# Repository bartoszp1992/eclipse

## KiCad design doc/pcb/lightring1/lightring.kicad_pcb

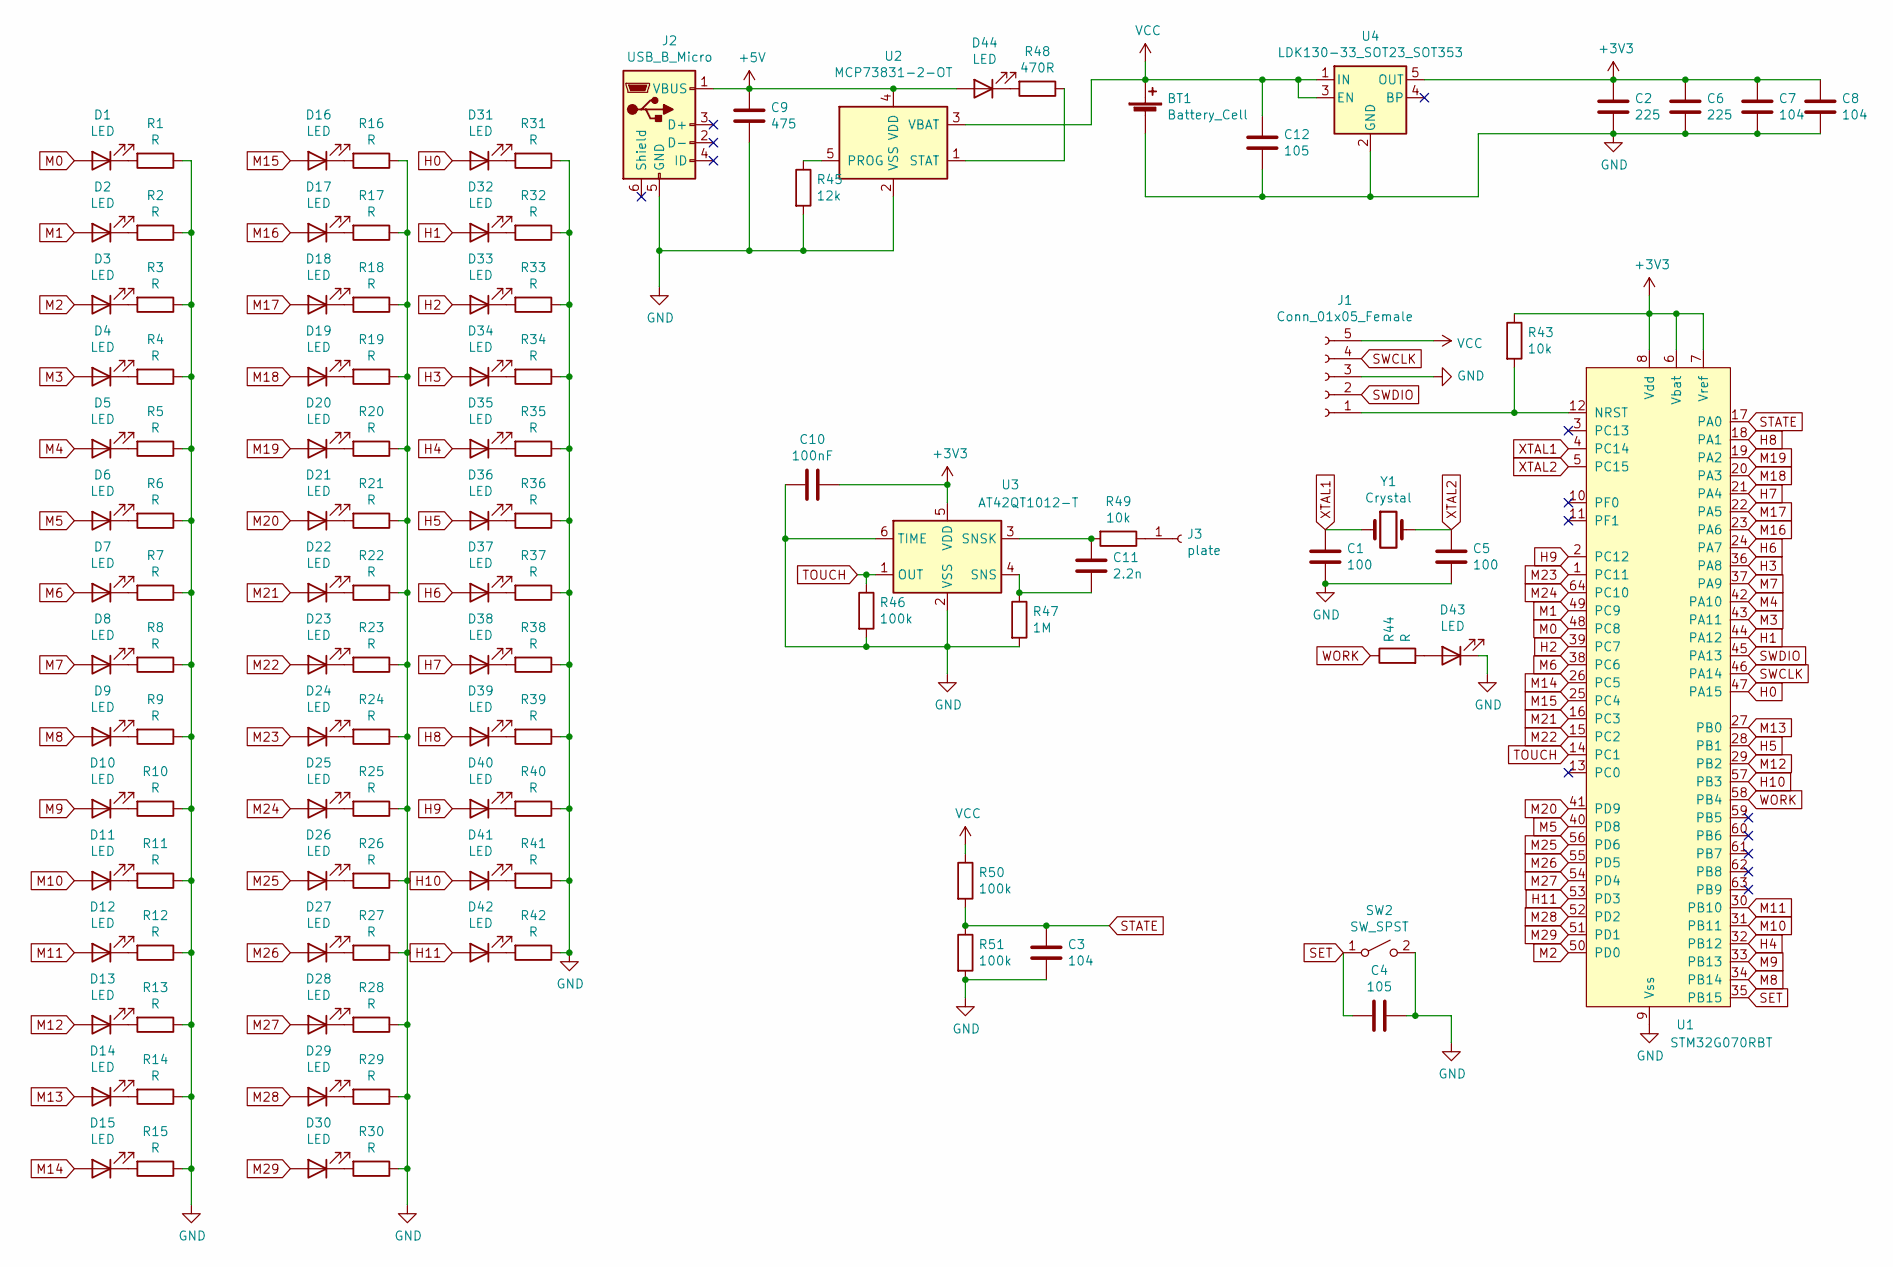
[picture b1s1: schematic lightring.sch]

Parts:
BT1: Battery_Cell; R_1210_3225Metric
C1, C5: 100; C_0603_1608Metric
C2, C6: 225; C_0603_1608Metric
C3, C7, C8: 104; C_0603_1608Metric
C4, C12: 105; C_0603_1608Metric
C9: 475; C_0603_1608Metric
C10: 100nF; C_0603_1608Metric
C11: 2.2n; C_0603_1608Metric
D1, D2, D3, D4, D5, D6, D7, D8, D9, D10, D11, D12, D13, D14, D15, D16, D17, D18, D19, D20, D21, D22, D23, D24, D25, D26, D27, D28, D29, D30, D31, D32, D33, D34, D35, D36, D37, D38, D39, D40, D41, D42, D43: LED; LR_LED
D44: LED; D_0603_1608Metric
J1: Conn_01x05_Female; PinHeader_1x05_P1.27mm_Vertical
J2: USB_B_Micro; USB_Micro-B_Molex_47346-0001
J3: plate; touchplate
R1, R2, R3, R4, R5, R6, R7, R8, R9, R10, R11, R12, R13, R14, R15, R16, R17, R18, R19, R20, R21, R22, R23, R24, R25, R26, R27, R28, R29, R30, R31, R32, R33, R34, R35, R36, R37, R38, R39, R40, R41, R42: R; LR_RES
R43, R49: 10k; R_0603_1608Metric
R44: R; R_0603_1608Metric
R45: 12k; R_0603_1608Metric
R46, R50, R51: 100k; R_0603_1608Metric
R47: 1M; R_0603_1608Metric
R48: 470R; R_0603_1608Metric
SW2: SW_SPST; Panasonic_EVQPUJ_EVQPUA
U1: STM32G070RBT; LQFP-64_10x10mm_P0.5mm
U2: MCP73831-2-OT; SOT-23-5
U3: AT42QT1012-T; SOT-23-6
U4: LDK130-33_SOT23_SOT353; SOT-23-5
Y1: Crystal; Crystal_C26-LF_D2.1mm_L6.5mm_Horizontal

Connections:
+3V3: C2.1, C6.1, C7.1, C8.1, C10.1, R43.1, U1.6 (Vbat), U1.7 (Vref), U1.8 (Vdd), U3.5 (VDD), U4.5 (OUT)
+5V: C9.1, D44.2 (A), J2.1 (VBUS), U2.4 (VDD)
GND: BT1.2 (-), C1.2, C2.2, C3.2, C4.1, C5.2, C6.2, C7.2, C8.2, C9.2, C10.2, C12.2, D43.1 (K), J1.3, J2.5 (GND), R1.1, R2.1, R3.1, R4.1, R5.1, R6.1, R7.1, R8.1, R9.1, R10.1, R11.1, R12.1, R13.1, R14.1, R15.1, R16.1, R17.1, R18.1, R19.1, R20.1, R21.1, R22.1, R23.1, R24.1, R25.1, R26.1, R27.1, R28.1, R29.1, R30.1, R31.1, R32.1, R33.1, R34.1, R35.1, R36.1, R37.1, R38.1, R39.1, R40.1, R41.1, R42.1, R45.2, R46.2, R47.2, R51.2, SW2.2 (B), U1.9 (Vss), U2.2 (VSS), U3.2 (VSS), U3.6 (TIME), U4.2 (GND)
H0: D31.2 (A), U1.47 (PA15)
H1: D32.2 (A), U1.44 (PA12)
H2: D33.2 (A), U1.39 (PC7)
H3: D34.2 (A), U1.36 (PA8)
H4: D35.2 (A), U1.32 (PB12)
H5: D36.2 (A), U1.28 (PB1)
H6: D37.2 (A), U1.24 (PA7)
H7: D38.2 (A), U1.21 (PA4)
H8: D39.2 (A), U1.18 (PA1)
H9: D40.2 (A), U1.2 (PC12)
H10: D41.2 (A), U1.57 (PB3)
H11: D42.2 (A), U1.53 (PD3)
M0: D1.2 (A), U1.48 (PC8)
M1: D2.2 (A), U1.49 (PC9)
M2: D3.2 (A), U1.50 (PD0)
M3: D4.2 (A), U1.43 (PA11)
M4: D5.2 (A), U1.42 (PA10)
M5: D6.2 (A), U1.40 (PD8)
M6: D7.2 (A), U1.38 (PC6)
M7: D8.2 (A), U1.37 (PA9)
M8: D9.2 (A), U1.34 (PB14)
M9: D10.2 (A), U1.33 (PB13)
M10: D11.2 (A), U1.31 (PB11)
M11: D12.2 (A), U1.30 (PB10)
M12: D13.2 (A), U1.29 (PB2)
M13: D14.2 (A), U1.27 (PB0)
M14: D15.2 (A), U1.26 (PC5)
M15: D16.2 (A), U1.25 (PC4)
M16: D17.2 (A), U1.23 (PA6)
M17: D18.2 (A), U1.22 (PA5)
M18: D19.2 (A), U1.20 (PA3)
M19: D20.2 (A), U1.19 (PA2)
M20: D21.2 (A), U1.41 (PD9)
M21: D22.2 (A), U1.16 (PC3)
M22: D23.2 (A), U1.15 (PC2)
M23: D24.2 (A), U1.1 (PC11)
M24: D25.2 (A), U1.64 (PC10)
M25: D26.2 (A), U1.56 (PD6)
M26: D27.2 (A), U1.55 (PD5)
M27: D28.2 (A), U1.54 (PD4)
M28: D29.2 (A), U1.52 (PD2)
M29: D30.2 (A), U1.51 (PD1)
unnamed: C11.1, R49.2, U3.3 (SNSK)
unnamed: C11.2, R47.1, U3.4 (SNS)
unnamed: D1.1 (K), R1.2
unnamed: D2.1 (K), R2.2
unnamed: D3.1 (K), R3.2
unnamed: D4.1 (K), R4.2
unnamed: D5.1 (K), R5.2
unnamed: D6.1 (K), R6.2
unnamed: D7.1 (K), R7.2
unnamed: D8.1 (K), R8.2
unnamed: D9.1 (K), R9.2
unnamed: D10.1 (K), R10.2
unnamed: D11.1 (K), R11.2
unnamed: D12.1 (K), R12.2
unnamed: D13.1 (K), R13.2
unnamed: D14.1 (K), R14.2
unnamed: D15.1 (K), R15.2
unnamed: D16.1 (K), R16.2
unnamed: D17.1 (K), R17.2
unnamed: D18.1 (K), R18.2
unnamed: D19.1 (K), R19.2
unnamed: D20.1 (K), R20.2
unnamed: D21.1 (K), R21.2
unnamed: D22.1 (K), R22.2
unnamed: D23.1 (K), R23.2
unnamed: D24.1 (K), R24.2
unnamed: D25.1 (K), R25.2
unnamed: D26.1 (K), R26.2
unnamed: D27.1 (K), R27.2
unnamed: D28.1 (K), R28.2
unnamed: D29.1 (K), R29.2
unnamed: D30.1 (K), R30.2
unnamed: D31.1 (K), R31.2
unnamed: D32.1 (K), R32.2
unnamed: D33.1 (K), R33.2
unnamed: D34.1 (K), R34.2
unnamed: D35.1 (K), R35.2
unnamed: D36.1 (K), R36.2
unnamed: D37.1 (K), R37.2
unnamed: D38.1 (K), R38.2
unnamed: D39.1 (K), R39.2
unnamed: D40.1 (K), R40.2
unnamed: D41.1 (K), R41.2
unnamed: D42.1 (K), R42.2
unnamed: D43.2 (A), R44.2
unnamed: D44.1 (K), R48.2
unnamed: J1.1, R43.2, U1.12 (NRST)
unnamed: J3.1, R49.1
unnamed: R45.1, U2.5 (PROG)
unnamed: R48.1, U2.1 (STAT)
SET: C4.2, SW2.1 (A), U1.35 (PB15)
STATE: C3.1, R50.2, R51.1, U1.17 (PA0)
SWCLK: J1.4, U1.46 (PA14)
SWDIO: J1.2, U1.45 (PA13)
TOUCH: R46.1, U1.14 (PC1), U3.1 (OUT)
VCC: BT1.1 (+), C12.1, J1.5, R50.1, U2.3 (VBAT), U4.1 (IN), U4.3 (EN)
WORK: R44.1, U1.58 (PB4)
XTAL1: C1.1, U1.4 (PC14), Y1.1
XTAL2: C5.1, U1.5 (PC15), Y1.2

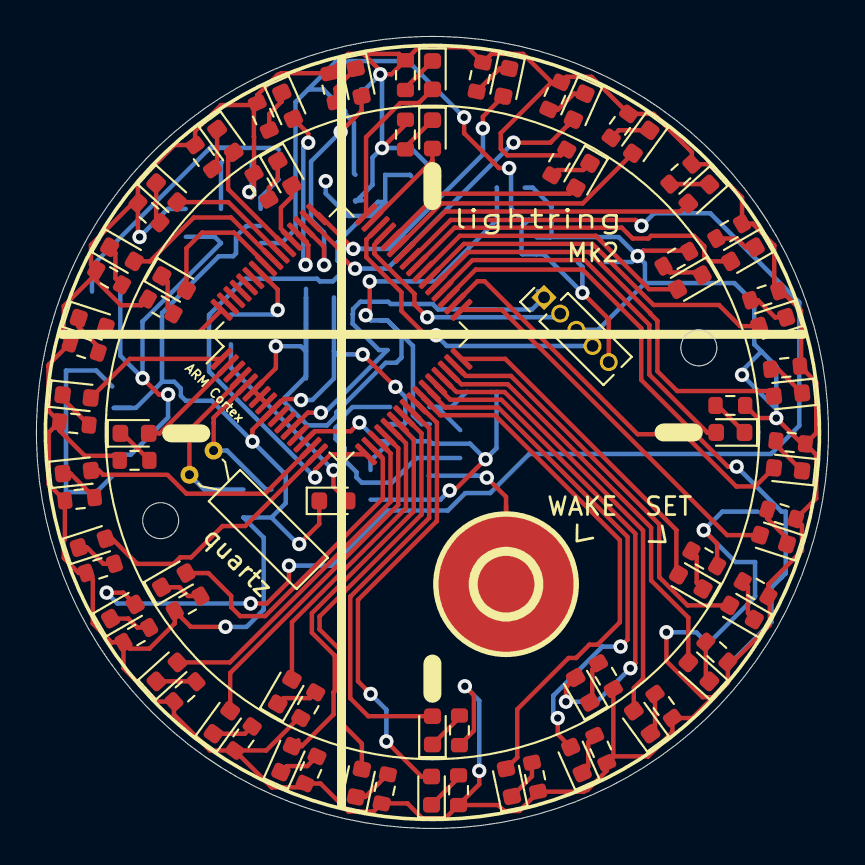
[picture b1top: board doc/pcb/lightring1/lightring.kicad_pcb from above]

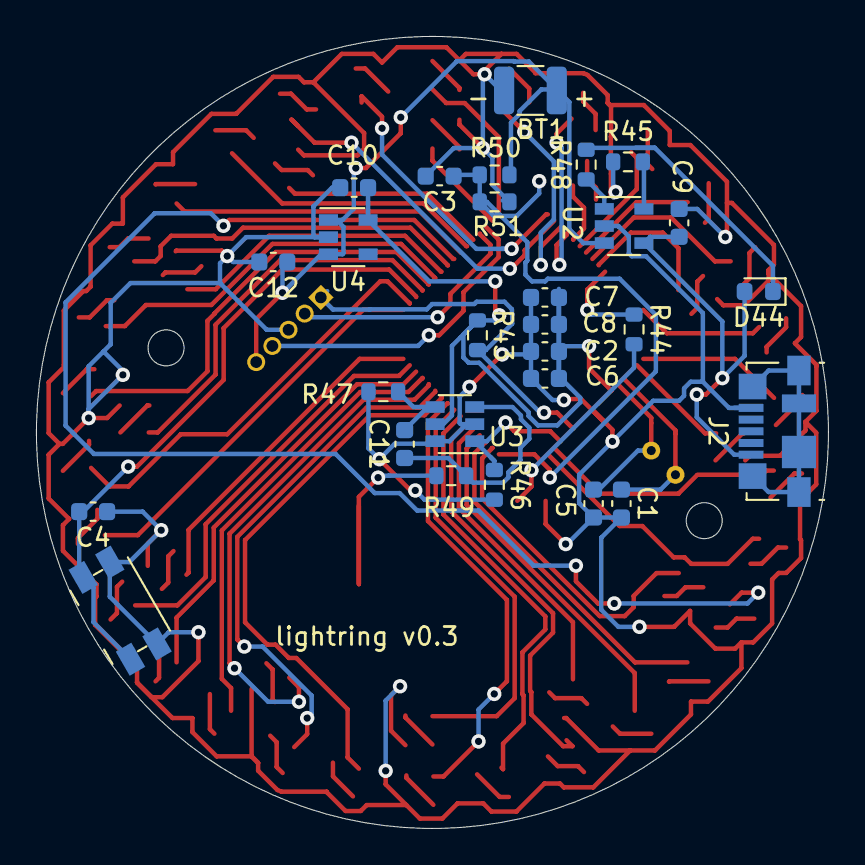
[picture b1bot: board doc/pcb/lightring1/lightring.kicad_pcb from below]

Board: 2 copper layers, 44.0 x 44.0 mm, 117 parts (28 on the bottom side), 104 nets.

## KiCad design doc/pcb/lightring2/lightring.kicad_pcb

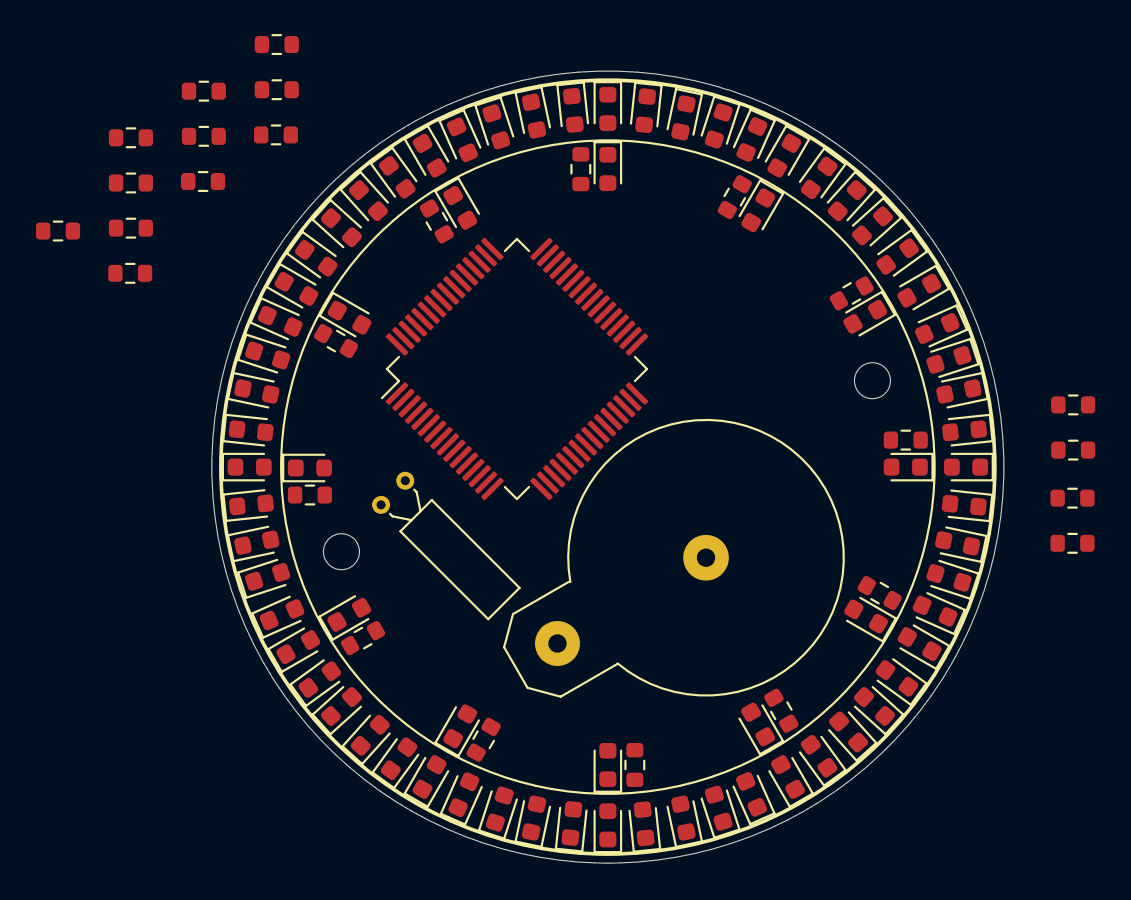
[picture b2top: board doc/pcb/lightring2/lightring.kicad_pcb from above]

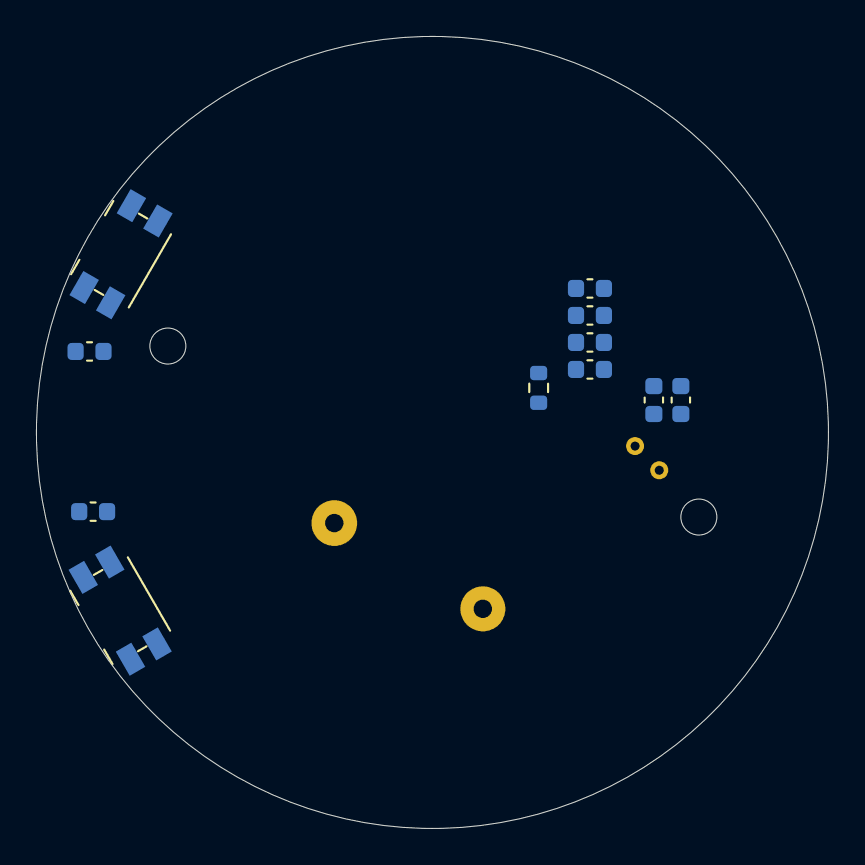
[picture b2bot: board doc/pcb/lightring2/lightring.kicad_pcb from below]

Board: 2 copper layers, 44.0 x 44.0 mm, 113 parts (11 on the bottom side), 38 nets, no tracks yet.

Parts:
BT1: Battery_Cell; BatteryHolder_Keystone_500
C1, C4: 100; LC_CAP
C2, C3: 105; LC_CAP
C5, C6: 225; LC_CAP
C7, C8: 104; LC_CAP
D1, D2, D3, D4, D5, D6, D7, D8, D9, D10, D11, D12, D13, D14, D15, D16, D17, D18, D19, D20, D21, D22, D23, D24, D25, D26, D27, D28, D29, D30, D31, D32, D33, D34, D35, D36, D37, D38, D39, D40, D41, D42, D43, D44, D45, D46, D47, D48, D49, D50, D51, D52, D53, D54, D55, D56, D57, D58, D59, D60, D61, D62, D63, D64, D65, D66, D67, D68, D69, D70, D71, D72: LED; LR_LED
R1, R2, R3, R4, R5, R6, R7, R8, R9, R10, R11, R12, R14, R15, R16, R17, R18, R19, R20, R21, R22, R23, R24, R25, R26, R27, R28: R; LR_RES
R13: 10k; LR_RES
SW1, SW2: SW_SPST; Panasonic_EVQPUJ_EVQPUA
U1: STM32G070RBT; LQFP-64_10x10mm_P0.5mm
Y1: Crystal; Crystal_C26-LF_D2.1mm_L6.5mm_Horizontal

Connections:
GND: BT1.2, C1.2, C2.1, C3.1, C4.2, C5.2, C6.2, C7.2, C8.2, R1.1, R2.1, R3.1, R4.1, R5.1, R6.1, R7.1, R8.1, R9.1, R10.1, R11.1, R12.1, SW1.2, SW2.2, U1.9
unnamed: D1.2, D16.2, D31.2, D46.2, R14.1
unnamed: D10.2, D25.2, D40.2, D55.2, R23.1
unnamed: D11.2, D26.2, D41.2, D56.2, R24.1
unnamed: D12.2, D27.2, D42.2, D57.2, R25.1
unnamed: D13.2, D28.2, D43.2, D58.2, R26.1
unnamed: D14.2, D29.2, D44.2, D59.2, R27.1
unnamed: D15.2, D30.2, D45.2, D60.2, R28.1
unnamed: D2.2, D17.2, D32.2, D47.2, R15.1
unnamed: D3.2, D18.2, D33.2, D48.2, R16.1
unnamed: D4.2, D19.2, D34.2, D49.2, R17.1
unnamed: D5.2, D20.2, D35.2, D50.2, R18.1
unnamed: D6.2, D21.2, D36.2, D51.2, R19.1
unnamed: D7.2, D22.2, D37.2, D52.2, R20.1
unnamed: D8.2, D23.2, D38.2, D53.2, R21.1
unnamed: D9.2, D24.2, D39.2, D54.2, R22.1
unnamed: D61.1, R1.2
unnamed: D62.1, R2.2
unnamed: D63.1, R3.2
unnamed: D64.1, R4.2
unnamed: D65.1, R5.2
unnamed: D66.1, R6.2
unnamed: D67.1, R7.2
unnamed: D68.1, R8.2
unnamed: D69.1, R9.2
unnamed: D70.1, R10.2
unnamed: D71.1, R11.2
unnamed: D72.1, R12.2
unnamed: R13.2, U1.12
Q0: D1.1, D2.1, D3.1, D4.1, D5.1, D6.1, D7.1, D8.1, D9.1, D10.1, D11.1, D12.1, D13.1, D14.1, D15.1
Q1: D16.1, D17.1, D18.1, D19.1, D20.1, D21.1, D22.1, D23.1, D24.1, D25.1, D26.1, D27.1, D28.1, D29.1, D30.1
Q2: D31.1, D32.1, D33.1, D34.1, D35.1, D36.1, D37.1, D38.1, D39.1, D40.1, D41.1, D42.1, D43.1, D44.1, D45.1
Q3: D46.1, D47.1, D48.1, D49.1, D50.1, D51.1, D52.1, D53.1, D54.1, D55.1, D56.1, D57.1, D58.1, D59.1, D60.1
SET: C3.2, SW2.1
VCC: BT1.1, C5.1, C6.1, C7.1, C8.1, R13.1, U1.6, U1.7, U1.8
WAKE: C2.2, SW1.1
XTAL1: C1.1, U1.3, Y1.1
XTAL2: C4.1, U1.4, Y1.2

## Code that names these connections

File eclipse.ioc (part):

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PB13.GPIOParameters=GPIO_Label
PC7.GPIOParameters=GPIO_Label
Mcu.UserName=STM32G070RBTx
PD9.GPIOParameters=GPIO_Label
PA11\ [PA9].GPIO_Label=M3
PC12.Signal=GPIO_Output
PA12\ [PA10].GPIO_Label=H1
PC10.Signal=GPIO_Output
PB14.GPIO_Label=M8
PD3.GPIOParameters=GPIO_Label
PA0.GPIO_Label=STATE
PA14-BOOT0.Mode=Serial_Wire
PA9.GPIOParameters=GPIO_Label
PC6.GPIO_Label=M6
PD0.GPIO_Label=M2
PA3.GPIOParameters=GPIO_Label
PB0.GPIO_Label=M13
PA6.GPIO_Label=M16
PD2.GPIOParameters=GPIO_Label
PC15-OSC32_OUT\ (PC15).Mode=LSE-External-Oscillator
PB13.GPIO_Label=M9
PB11.Signal=GPIO_Output
PB13.Signal=GPIO_Output
PB15.Signal=GPXTI15
PD6.GPIO_Label=M25
PA2.GPIOParameters=GPIO_Label
PC14-OSC32_IN\ (PC14).Mode=LSE-External-Oscillator
PA15.GPIO_Label=H0
PB4.GPIOParameters=GPIO_Label
PC1.GPIOParameters=GPIO_Label,GPIO_ModeDefaultEXTI
PA12\ [PA10].Signal=GPIO_Output
PD4.Signal=GPIO_Output
PC7.Signal=GPIO_Output
PD8.GPIOParameters=GPIO_Label
PC3.Signal=GPIO_Output
PA8.GPIOParameters=GPIO_Label
PD0.Signal=GPIO_Output
PD8.Signal=GPIO_Output
PA14-BOOT0.Signal=SYS_SWCLK
RCC.HSE_VALUE=8000000
PA11\ [PA9].GPIOParameters=GPIO_Label
PB2.Signal=GPIO_Output
PD1.GPIOParameters=GPIO_Label
PD1.GPIO_Label=M29
PB12.GPIO_Label=H4
PA12\ [PA10].GPIOParameters=GPIO_Label
PB0.GPIOParameters=GPIO_Label
PA1.GPIOParameters=GPIO_Label
PC4.GPIO_Label=M15
PB1.GPIO_Label=H5
PC11.GPIO_Label=M23
PA10.GPIO_Label=M4
PA0.Mode=IN0
PB3.GPIOParameters=GPIO_Label
PA8.Signal=GPIO_Output
PA0.Signal=ADC1_IN0
PC8.GPIOParameters=GPIO_Label
Mcu.Package=LQFP64
PB1.Signal=GPIO_Output
PA6.Signal=GPIO_Output
PB15.GPIO_PuPd=GPIO_PULLUP
PD5.GPIO_Label=M26
PD5.GPIOParameters=GPIO_Label
PA2.GPIO_Label=M19
PA10.Signal=GPIO_Output
PA15.Signal=GPIO_Output
PA5.GPIOParameters=GPIO_Label
PB14.GPIOParameters=GPIO_Label
PC5.Signal=GPIO_Output
PD3.GPIO_Label=H11
PB10.GPIOParameters=GPIO_Label
PD6.Signal=GPIO_Output
PA4.GPIO_Label=H7
PC2.GPIO_Label=M22
PC4.GPIOParameters=GPIO_Label
PB4.Signal=GPIO_Output
PA3.Signal=GPIO_Output
PB3.GPIO_Label=H10
PA6.GPIOParameters=GPIO_Label
PD6.GPIOParameters=GPIO_Label
PD9.GPIO_Label=M20
PA15.GPIOParameters=GPIO_Label
PC10.GPIO_Label=M24
PC9.GPIO_Label=M1
PA9.GPIO_Label=M7
PC11.Signal=GPIO_Output
PD3.Signal=GPIO_Output
PC8.Signal=GPIO_Output
PC2.Signal=GPIO_Output
PC4.Signal=GPIO_Output
PC6.Signal=GPIO_Output
PB11.GPIO_Label=M10
PD1.Signal=GPIO_Output
PC15-OSC32_OUT\ (PC15).Signal=RCC_OSC32_OUT
PD9.Signal=GPIO_Output
PD5.Signal=GPIO_Output
PC11.GPIOParameters=GPIO_Label
PD8.GPIO_Label=M5
PC3.GPIOParameters=GPIO_Label
PC12.GPIOParameters=GPIO_Label
PC8.GPIO_Label=M0
PA13.Signal=SYS_SWDIO
PA8.GPIO_Label=H3
PB10.GPIO_Label=M11
PC5.GPIOParameters=GPIO_Label
PB2.GPIOParameters=GPIO_Label
PA9.Signal=GPIO_Output
PB11.GPIOParameters=GPIO_Label
PA1.Signal=GPIO_Output
PB10.Signal=GPIO_Output
PB14.Signal=GPIO_Output
PA5.Signal=GPIO_Output
PB15.GPIO_ModeDefaultEXTI=GPIO_MODE_IT_FALLING
board=custom
PB4.GPIO_Label=WORK
PB15.GPIO_Label=SET
PD4.GPIO_Label=M27
PC2.GPIOParameters=GPIO_Label
PA1.GPIO_Label=H8
PC1.GPIO_Label=TOUCH
PA10.GPIOParameters=GPIO_Label
PD4.GPIOParameters=GPIO_Label
PA4.GPIOParameters=GPIO_Label
PC10.GPIOParameters=GPIO_Label
PB15.GPIOParameters=GPIO_PuPd,GPIO_Label,GPIO_ModeDefaultEXTI
PA13.Mode=Serial_Wire
PC9.GPIOParameters=GPIO_Label
Mcu.Name=STM32G070RBTx
PA11\ [PA9].Signal=GPIO_Output
PA2.Signal=GPIO_Output
PC7.GPIO_Label=H2
PB3.Signal=GPIO_Output
PA4.Signal=GPIO_Output
RCC.SYSCLKFreq_VALUE=16000000
PA7.GPIO_Label=H6
PA5.GPIO_Label=M17
PC5.GPIO_Label=M14
PC14-OSC32_IN\ (PC14).Signal=RCC_OSC32_IN
PC12.GPIO_Label=H9
PB2.GPIO_Label=M12
PA0.GPIOParameters=GPIO_Label
PC6.GPIOParameters=GPIO_Label
PD0.GPIOParameters=GPIO_Label
PC1.GPIO_ModeDefaultEXTI=GPIO_MODE_IT_RISING_FALLING
PC3.GPIO_Label=M21
PC9.Signal=GPIO_Output
PD2.Signal=GPIO_Output
PB0.Signal=GPIO_Output
PA7.GPIOParameters=GPIO_Label
PC1.Signal=GPXTI1
PB12.GPIOParameters=GPIO_Label
PB12.Signal=GPIO_Output
PD2.GPIO_Label=M28
PA3.GPIO_Label=M18
PB1.GPIOParameters=GPIO_Label
PA7.Signal=GPIO_Output

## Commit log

2020-12-03 initial
2020-12-05 finished PCB
2020-12-20 v2 base board
2020-12-25 v0.2 board
2021-01-19 testing program
2021-01-20 initial program
2021-01-21 working program
2021-01-21 silks corrections
2021-01-21 working seconds and forcce mode
2021-01-22 corrections
2021-01-24 v0.3 PCB
2021-02-03 generated gerbers
2021-02-18 removed old pcb
2021-02-18 changed stabiliser
2021-02-18 changed to mk2 in base
2021-02-20 exported schematic
2021-06-08 added charger datasheet
